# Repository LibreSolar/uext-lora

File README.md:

# LoRa communication board based on HopeRF RFM95 for UEXT connector

Designed with KiCad 5.

## Features

- UEXT connector to communicate with host MCU
- Separate antenna connector

### Image

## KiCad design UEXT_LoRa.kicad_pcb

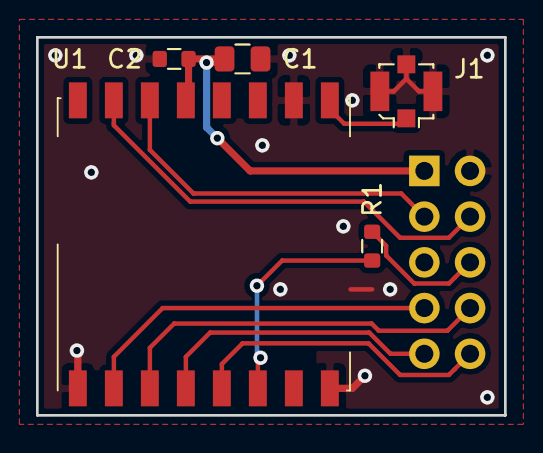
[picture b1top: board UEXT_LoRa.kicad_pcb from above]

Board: 2 copper layers, 26.0 x 21.0 mm, 6 parts (1 on the bottom side), 11 nets.

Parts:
C1: 10uF; C_0805_2012
C2: 100n; C_0603_1608
J1: Conn_Coaxial; U.FL_Molex_MCRF_73412-0110_Vertical
J2: UEXT; PinSocket_2x05_P2.54mm_Vertical
R1: 1k; R_0603_1608
U1: RFM95W-868S2; HOPERF_RFM9XW_SMD

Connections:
+3V3: C1.1, C2.1, J2.1, U1.13
/DIO0: J2.3, U1.14
/DIO1: J2.4, U1.15
/MISO: J2.7, U1.2
/MOSI: J2.8, U1.3
/SCK: J2.9, U1.4
/SSEL: J2.10, U1.5
/~RESET: J2.6, R1.2
GND: C1.2, C2.2, J1.2, J2.2, U1.1, U1.8, U1.10
unnamed: J1.1, U1.9
unnamed: R1.1, U1.6
